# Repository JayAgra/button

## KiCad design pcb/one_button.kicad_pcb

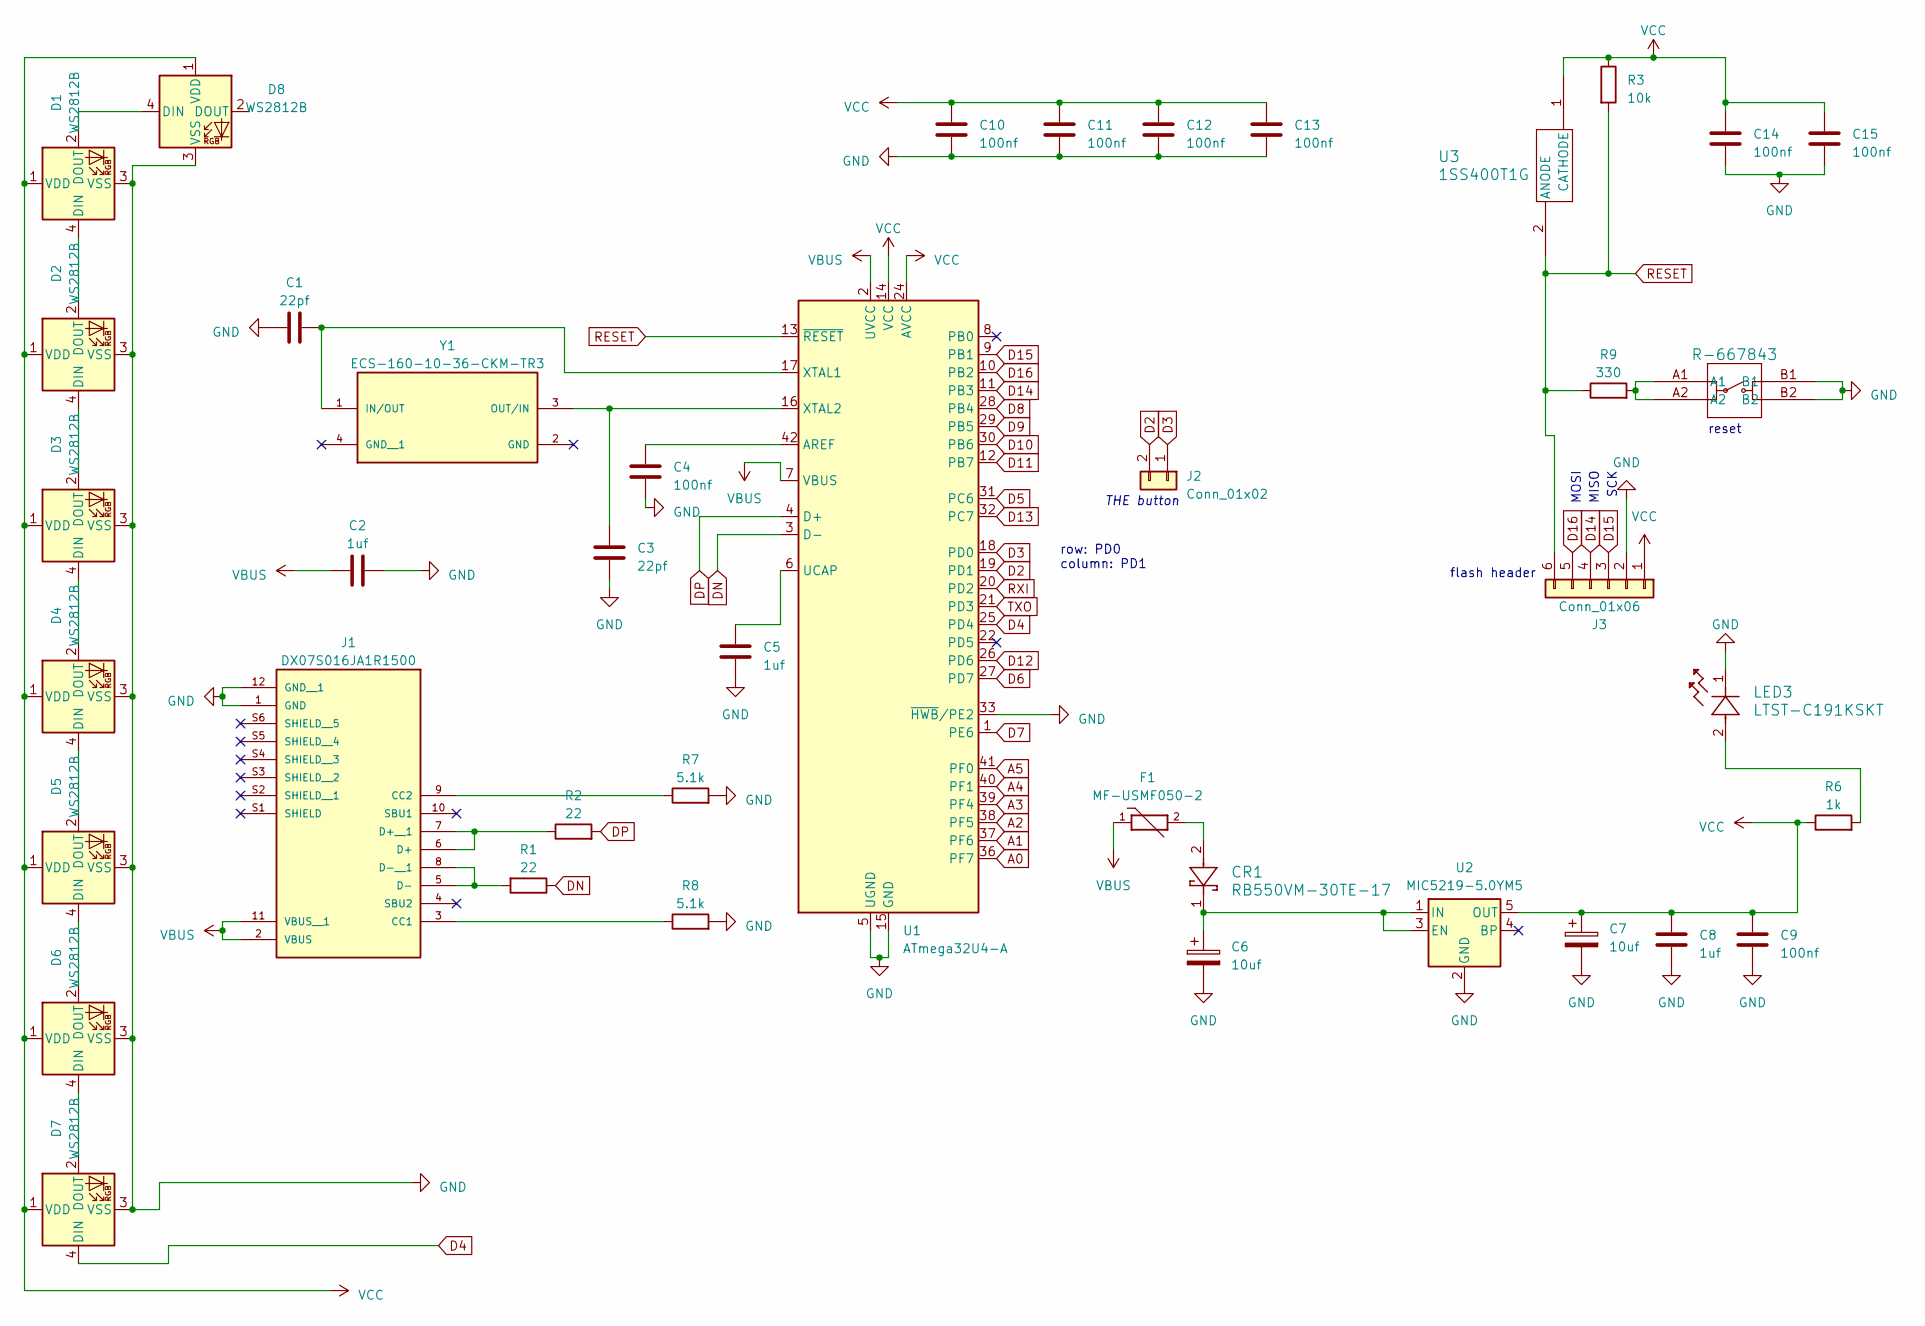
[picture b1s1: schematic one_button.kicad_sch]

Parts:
C1, C3: 22pf; C_0805_2012Metric
C2, C5, C8: 1uf; C_0805_2012Metric
C4, C9, C10, C11, C12, C13, C14, C15: 100nf; C_0805_2012Metric
C6, C7: 10uf; CP_EIA-3528-15_AVX-H_Pad1.50x2.35mm_HandSolder
CR1: RB550VM-30TE-17; SDO_RB550VM-30TE-17_ROM
D1, D2, D3, D4, D5, D6, D7, D8: WS2812B; LED_WS2812B_PLCC4_5.0x5.0mm_P3.2mm
F1: MF-USMF050-2; FUSER_MF-USMF050-2; PARTREV R
J1: DX07S016JA1R1500; JAE_DX07S016JA1R1500; PARTREV 1
J2: Conn_01x02; Kailh_socket_MX
J3: Conn_01x06; PinHeader_1x06_P2.54mm_Vertical
LED3: LTST-C191KSKT; LED_LTST-C191KRKT_LTO
R1, R2: 22; R_0805_2012Metric
R3: 10k; R_0805_2012Metric
R6: 1k; R_0805_2012Metric
R7, R8: 5.1k; R_0805_2012Metric
R9: 330; R_0805_2012Metric
SW1: R-667843; R-667843_MIT
U1: ATmega32U4-A; TQFP-44_10x10mm_P0.8mm
U2: MIC5219-5.0YM5; SOT-23-5
U3: 1SS400T1G; D_SOD-523
Y1: ECS-160-10-36-CKM-TR3; XTAL_ECS-160-10-36-CKM-TR3; PARTREV 2017

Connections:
A0: U1.36 (PF7)
A1: U1.37 (PF6)
A2: U1.38 (PF5)
A3: U1.39 (PF4)
A4: U1.40 (PF1)
A5: U1.41 (PF0)
D2: J2.2, U1.19 (PD1)
D3: J2.1, U1.18 (PD0)
D4: D7.4 (DIN), U1.25 (PD4)
D5: U1.31 (PC6)
D6: U1.27 (PD7)
D7: U1.1 (PE6)
D8: U1.28 (PB4)
D9: U1.29 (PB5)
D10: U1.30 (PB6)
D11: U1.12 (PB7)
D12: U1.26 (PD6)
D13: U1.32 (PC7)
D14: J3.4, U1.11 (PB3)
D15: J3.3, U1.9 (PB1)
D16: J3.5, U1.10 (PB2)
DN: R1.1, U1.3 (D-)
DP: R2.2, U1.4 (D+)
GND: C1.1, C2.2, C3.1, C4.2, C5.1, C6.2, C7.2, C8.2, C9.2, C10.2, C11.2, C12.2, C13.2, C14.2, C15.2, D1.3 (VSS), D2.3 (VSS), D3.3 (VSS), D4.3 (VSS), D5.3 (VSS), D6.3 (VSS), D7.3 (VSS), D8.3 (VSS), J1.1 (GND), J1.12 (GND__1), J3.2, LED3.1, R7.2, R8.2, SW1.B1, SW1.B2, U1.5 (UGND), U1.15 (GND), U1.23 (GND), U1.33 (~HWB/PE2), U1.35 (GND), U1.43 (GND), U2.2 (GND)
unnamed: CR1.2, F1.2
unnamed: D1.4 (DIN), D2.2 (DOUT)
unnamed: D1.2 (DOUT), D8.4 (DIN)
unnamed: D2.4 (DIN), D3.2 (DOUT)
unnamed: D3.4 (DIN), D4.2 (DOUT)
unnamed: D4.4 (DIN), D5.2 (DOUT)
unnamed: D5.4 (DIN), D6.2 (DOUT)
unnamed: D6.4 (DIN), D7.2 (DOUT)
unnamed: J1.3 (CC1), R8.1
unnamed: J1.9 (CC2), R7.1
unnamed: J1.6 (D+), J1.7 (D+__1), R2.1
unnamed: J1.5 (D-), J1.8 (D-__1), R1.2
unnamed: LED3.2, R6.2
unnamed: R9.2, SW1.A1, SW1.A2
unnamed: C4.1, U1.42 (AREF)
unnamed: C5.2, U1.6 (UCAP)
unnamed: C1.2, U1.17 (XTAL1), Y1.1 (IN/OUT)
unnamed: C3.2, U1.16 (XTAL2), Y1.3 (OUT/IN)
unnamed: C6.1, CR1.1, U2.1 (IN), U2.3 (EN)
RESET: J3.6, R3.2, R9.1, U1.13 (~RESET), U3.2 (ANODE)
RXI: U1.20 (PD2)
TXO: U1.21 (PD3)
VBUS: C2.1, F1.1, J1.2 (VBUS), J1.11 (VBUS__1), U1.2 (UVCC), U1.7 (VBUS)
VCC: C7.1, C8.1, C9.1, C10.1, C11.1, C12.1, C13.1, C14.1, C15.1, D1.1 (VDD), D2.1 (VDD), D3.1 (VDD), D4.1 (VDD), D5.1 (VDD), D6.1 (VDD), D7.1 (VDD), D8.1 (VDD), J3.1, R3.1, R6.1, U1.14 (VCC), U1.24 (AVCC), U1.34 (VCC), U1.44 (AVCC), U2.5 (OUT), U3.1 (CATHODE)

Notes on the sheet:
MOSI
THE button
MISO
flash header
reset
SCK
row: PD0 column: PD1

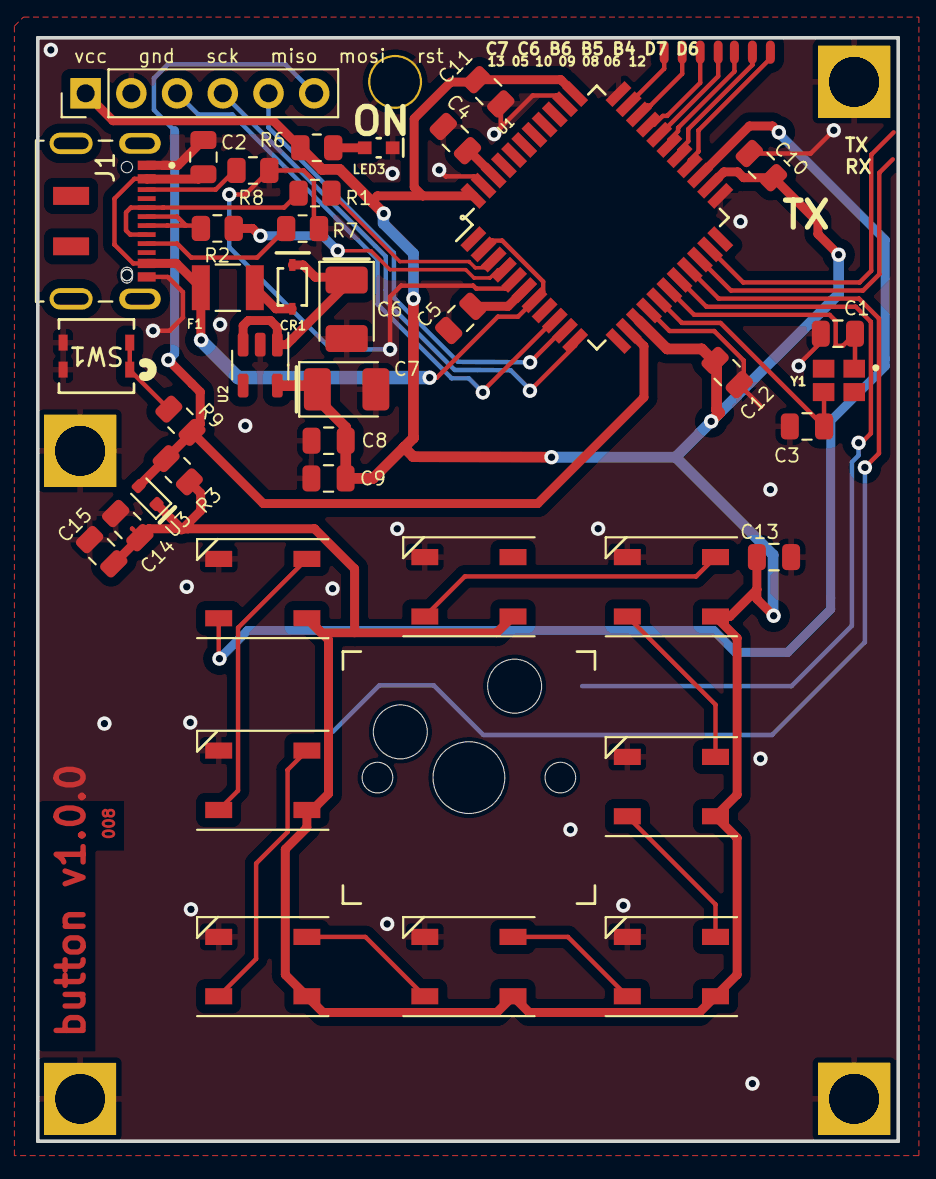
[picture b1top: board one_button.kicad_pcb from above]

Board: 2 copper layers, 47.8 x 61.3 mm, 41 parts (0 on the bottom side), 31 nets.

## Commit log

2023-12-05 add pcb
2023-12-05 ds store
2023-12-05 gerver revision 002
2023-12-05 gerber rev 003
2023-12-05 add reverse mounted led
2023-12-06 re-add mounting holes
2023-12-06 enshittify board
2023-12-06 cad 😭
2023-12-06 thicker walls
2023-12-09 finish case 1.0.0-004
2023-12-12 case 1.0.0.005
2023-12-19 rename
2023-12-19 lang settings
2024-01-03 fix pcb, firmware
